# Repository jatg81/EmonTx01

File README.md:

# EmonTx01
Medidor de energia

Medición de parametros eléctricos del tablero de alimentación mediante la tarjeta de hardware open source EmonTx Arduino Shield SMT, para realizar la medición de la corriente se utilizan 4 transformadores de corriente (total,tomacorrientes,luces y terma) y para medir el voltaje de red se utiliza un transformador de 220VAC a 9VAC
Los datos medidos son enviados al Raspberry Pi (EmonPi) mediante la tarjeta de RF RM69CW 433Mhz utilizando el protocolo RF12 de jeelib.

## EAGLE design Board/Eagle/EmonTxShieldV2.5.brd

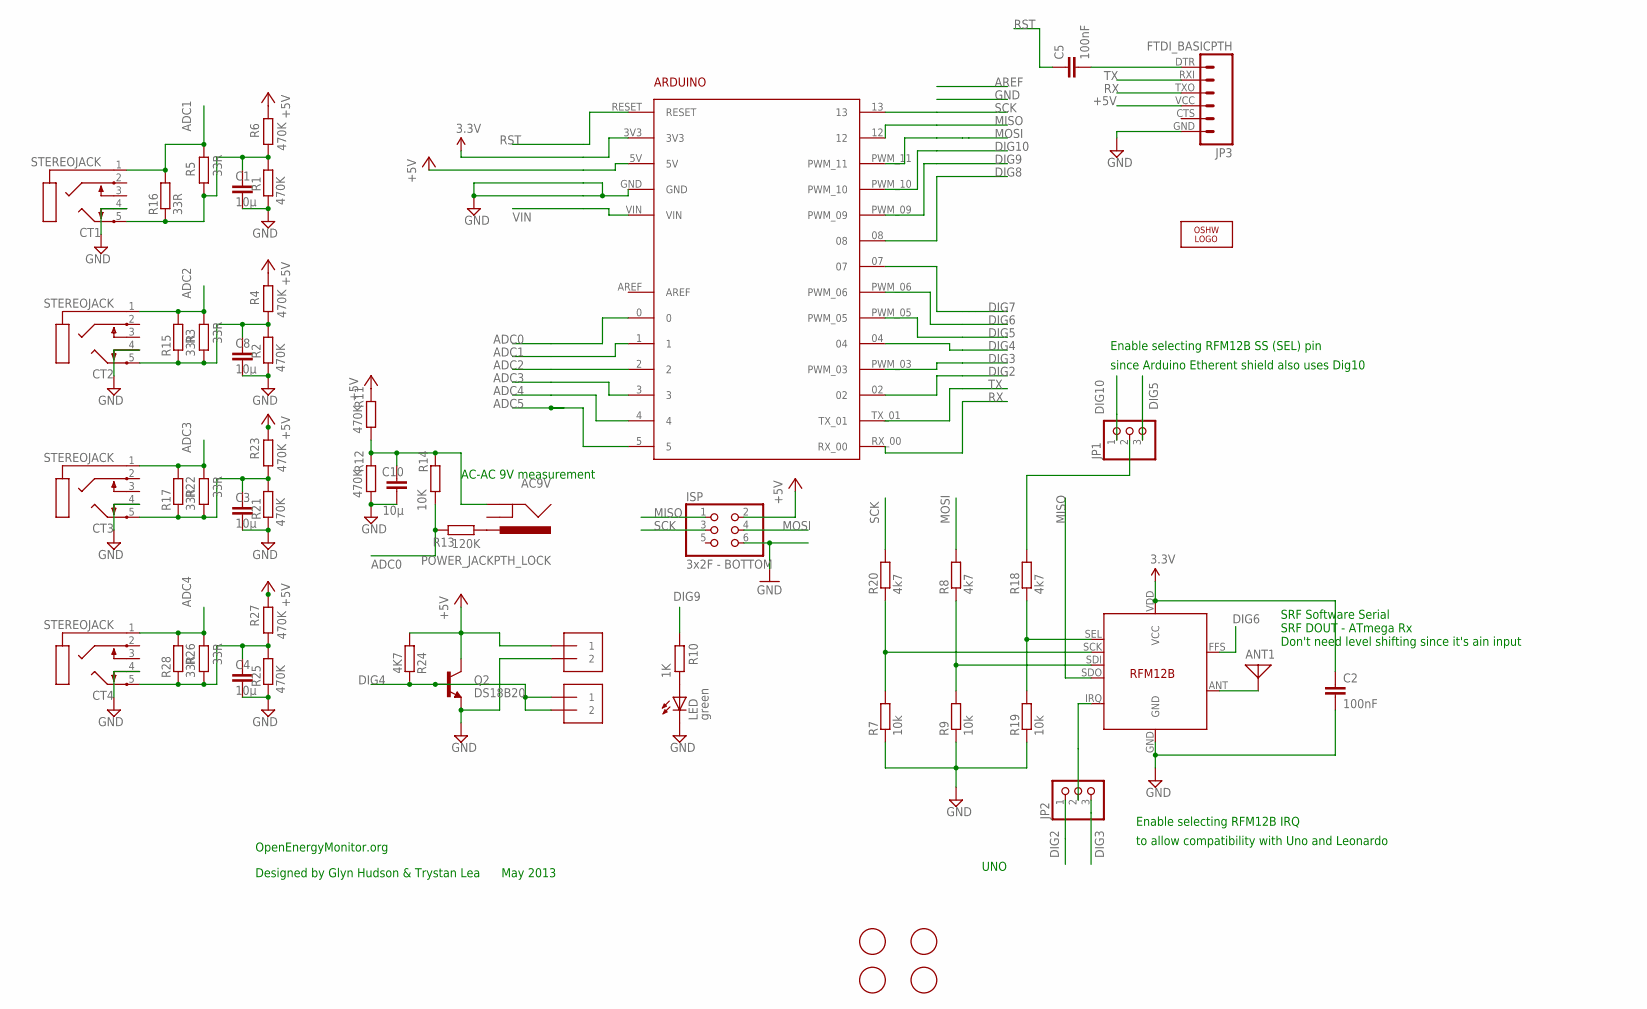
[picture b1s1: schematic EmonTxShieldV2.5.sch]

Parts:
AC9V: POWER_JACKPTH_LOCK; POWER_JACK_PTH_LOCK
ANT1: ANTENNA; PAD-01
ARDUINO1: ARDUINO2
C1, C3, C4, C8, C10: 10µ; C0603
C2, C5: 100nF; C0603
CT1, CT2, CT3, CT4: STEREOJACK; STX3100
ISP: 3x2F - BOTTOM; 2X03
J1, J2: 1X2-3.5MM
JP1, JP2: PINHD-1X3; 1X03
JP3: FTDI_BASICPTH; FTDI_BASIC
LED: green; CHIPLED_0805
LOGO1: OSHW_LOGO_10MILX0200-NT; OSHW_10X200_NOTEXT
Q2: DS18B20; TO-92
R1, R2, R4, R6, R11, R12, R21, R23, R25, R27: 470K; R0603
R3, R5, R22, R26: 33R; 0204/7
R7, R9, R19: 10k; R0603
R8, R18, R20: 4k7; R0603
R10: 1K; R0603
R13: 120K; R0603
R14: 10K; R0603
R15, R16, R17, R28: 33R; R1206
R24: 4K7; R0603
U$1, U$3, U$4, U$5: FIDUCIAL; FIDUCIAL_1MM
U$2: RFM12B

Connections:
3.3V: ARDUINO1.3V3, C2.1, U$2.VDD (VCC)
+5V: ARDUINO1.5V, ISP.2, J1.1, JP3.VCC (4), Q2.3 (C), R4.2, R6.2, R11.2, R23.2, R24.1, R27.2
ADC0: ARDUINO1.0, R13.2, R14.1
ADC1: ARDUINO1.1, CT1.1, R5.2, R16.2
ADC2: ARDUINO1.2, CT2.1, R3.2, R15.2
ADC3: ARDUINO1.3, CT3.1, R17.2, R22.2
ADC4: ARDUINO1.4, CT4.1, R26.2, R28.2
ADC5: ARDUINO1.5
DIG2: ARDUINO1.02, JP2.1
DIG3: ARDUINO1.PWM_03, JP2.3
DIG4: ARDUINO1.04, J2.1, J2.2, Q2.2 (B), R24.2
DIG5: ARDUINO1.PWM_05, JP1.3
DIG6: ARDUINO1.PWM_06, U$2.FFS
DIG7: ARDUINO1.07
DIG8: ARDUINO1.08
DIG9: ARDUINO1.PWM_09, R10.2
DIG10: ARDUINO1.PWM_10, JP1.1
GND: ARDUINO1.GND, C1.2, C2.2, C3.2, C4.2, C8.2, C10.2, CT1.4, CT2.4, CT3.4, CT4.4, ISP.6, J1.2, JP3.GND (6), LED.C, Q2.1 (E), R1.2, R2.2, R7.1, R9.1, R12.1, R19.1, R21.2, R25.2, U$2.GND
MISO: ARDUINO1.12, ISP.1, U$2.SDO
MOSI: ARDUINO1.PWM_11, ISP.4, R8.2
unnamed: JP2.2, U$2.IRQ
unnamed: JP1.2, R18.2
unnamed: C3.1, CT3.5, R17.1, R21.1, R22.1, R23.1
unnamed: C4.1, CT4.5, R25.1, R26.1, R27.1, R28.1
unnamed: AC9V.PWR, R13.1
unnamed: C5.2, JP3.DTR (1)
unnamed: C8.1, CT2.5, R2.1, R3.1, R4.1, R15.1
unnamed: AC9V.GND, C10.1, R11.1, R12.2, R14.2
unnamed: C1.1, CT1.5, R1.1, R5.1, R6.1, R16.1
unnamed: LED.A, R10.1
unnamed: ANT1.1, U$2.ANT
unnamed: R7.2, R20.1, U$2.SCK
unnamed: R8.1, R9.2, U$2.SDI
unnamed: R18.1, R19.2, U$2.SEL
RST: ARDUINO1.RESET, C5.1
RX: ARDUINO1.RX_00, JP3.TXO (3)
SCK: ARDUINO1.13, ISP.3, R20.2
TX: ARDUINO1.TX_01, JP3.RXI (2)
VIN: ARDUINO1.VIN

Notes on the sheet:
AC-AC 9V measurement
Enable selecting RFM12B SS (SEL) pin
since Arduino Etherent shield also uses Dig10
Enable selecting RFM12B IRQ
to allow compatibility with Uno and Leonardo
UNO
OpenEnergyMonitor.org
Designed by Glyn Hudson & Trystan Lea May 2013
SRF Software Serial SRF DOUT - ATmega Rx Don't need level shifting since it's ain input

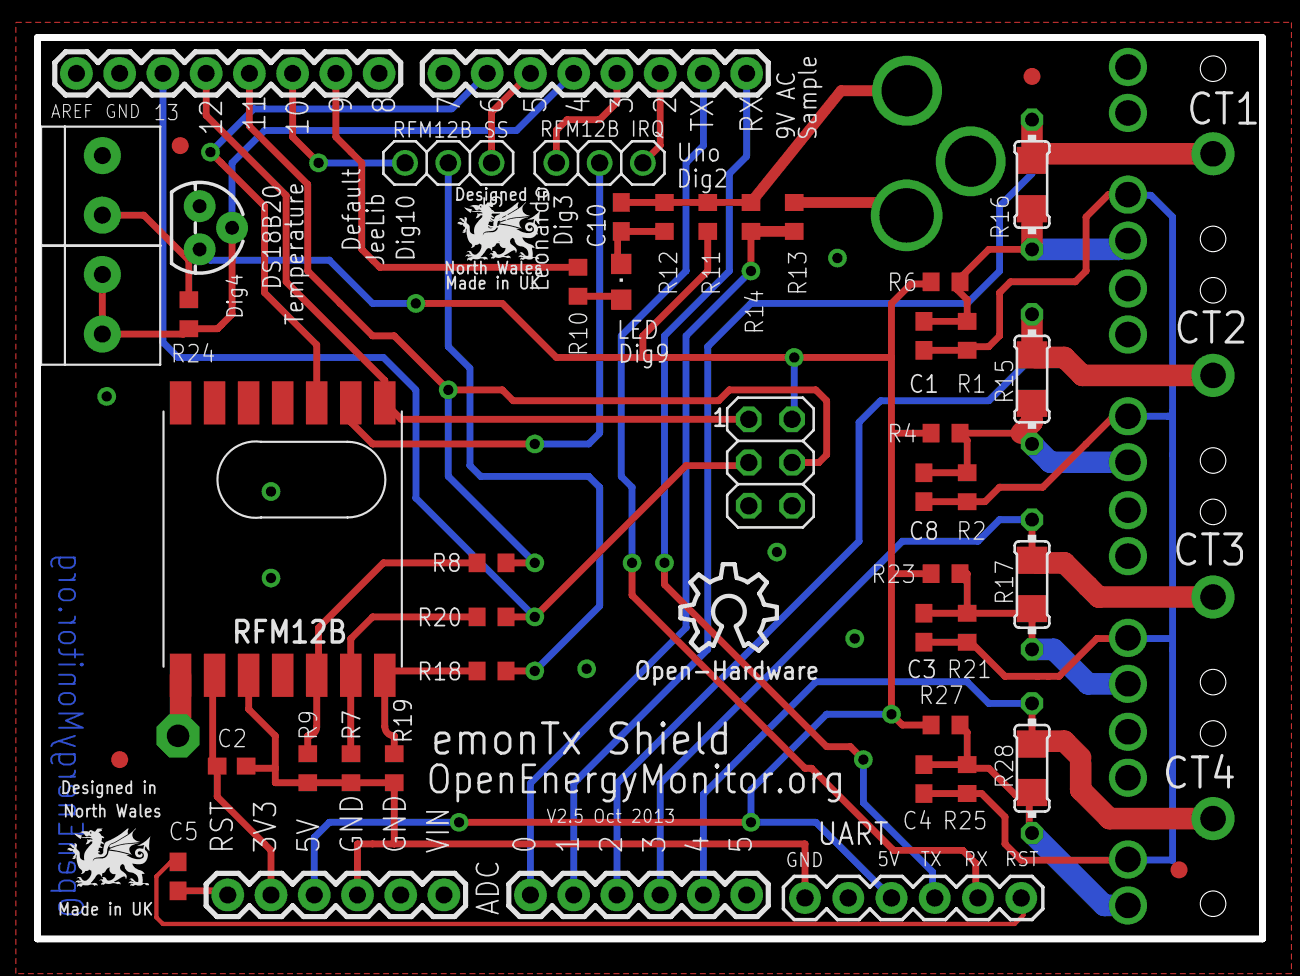
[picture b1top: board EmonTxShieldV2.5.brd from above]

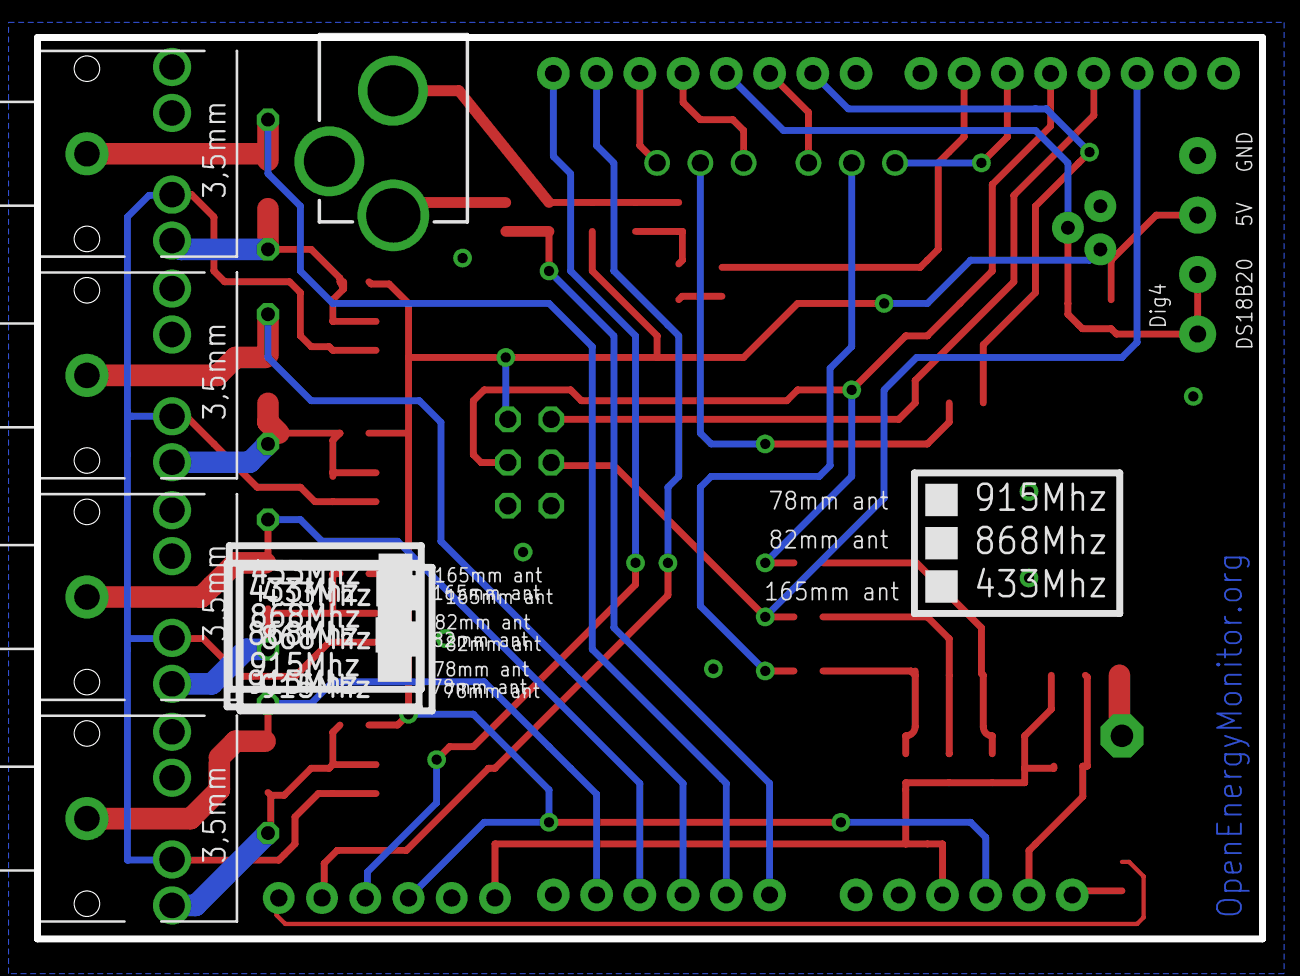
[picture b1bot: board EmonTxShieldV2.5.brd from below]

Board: 2 copper layers, 72.0 x 53.0 mm, 56 parts (5 on the bottom side), 35 nets.

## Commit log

2018-12-20 Create f
2018-12-20 Create d
